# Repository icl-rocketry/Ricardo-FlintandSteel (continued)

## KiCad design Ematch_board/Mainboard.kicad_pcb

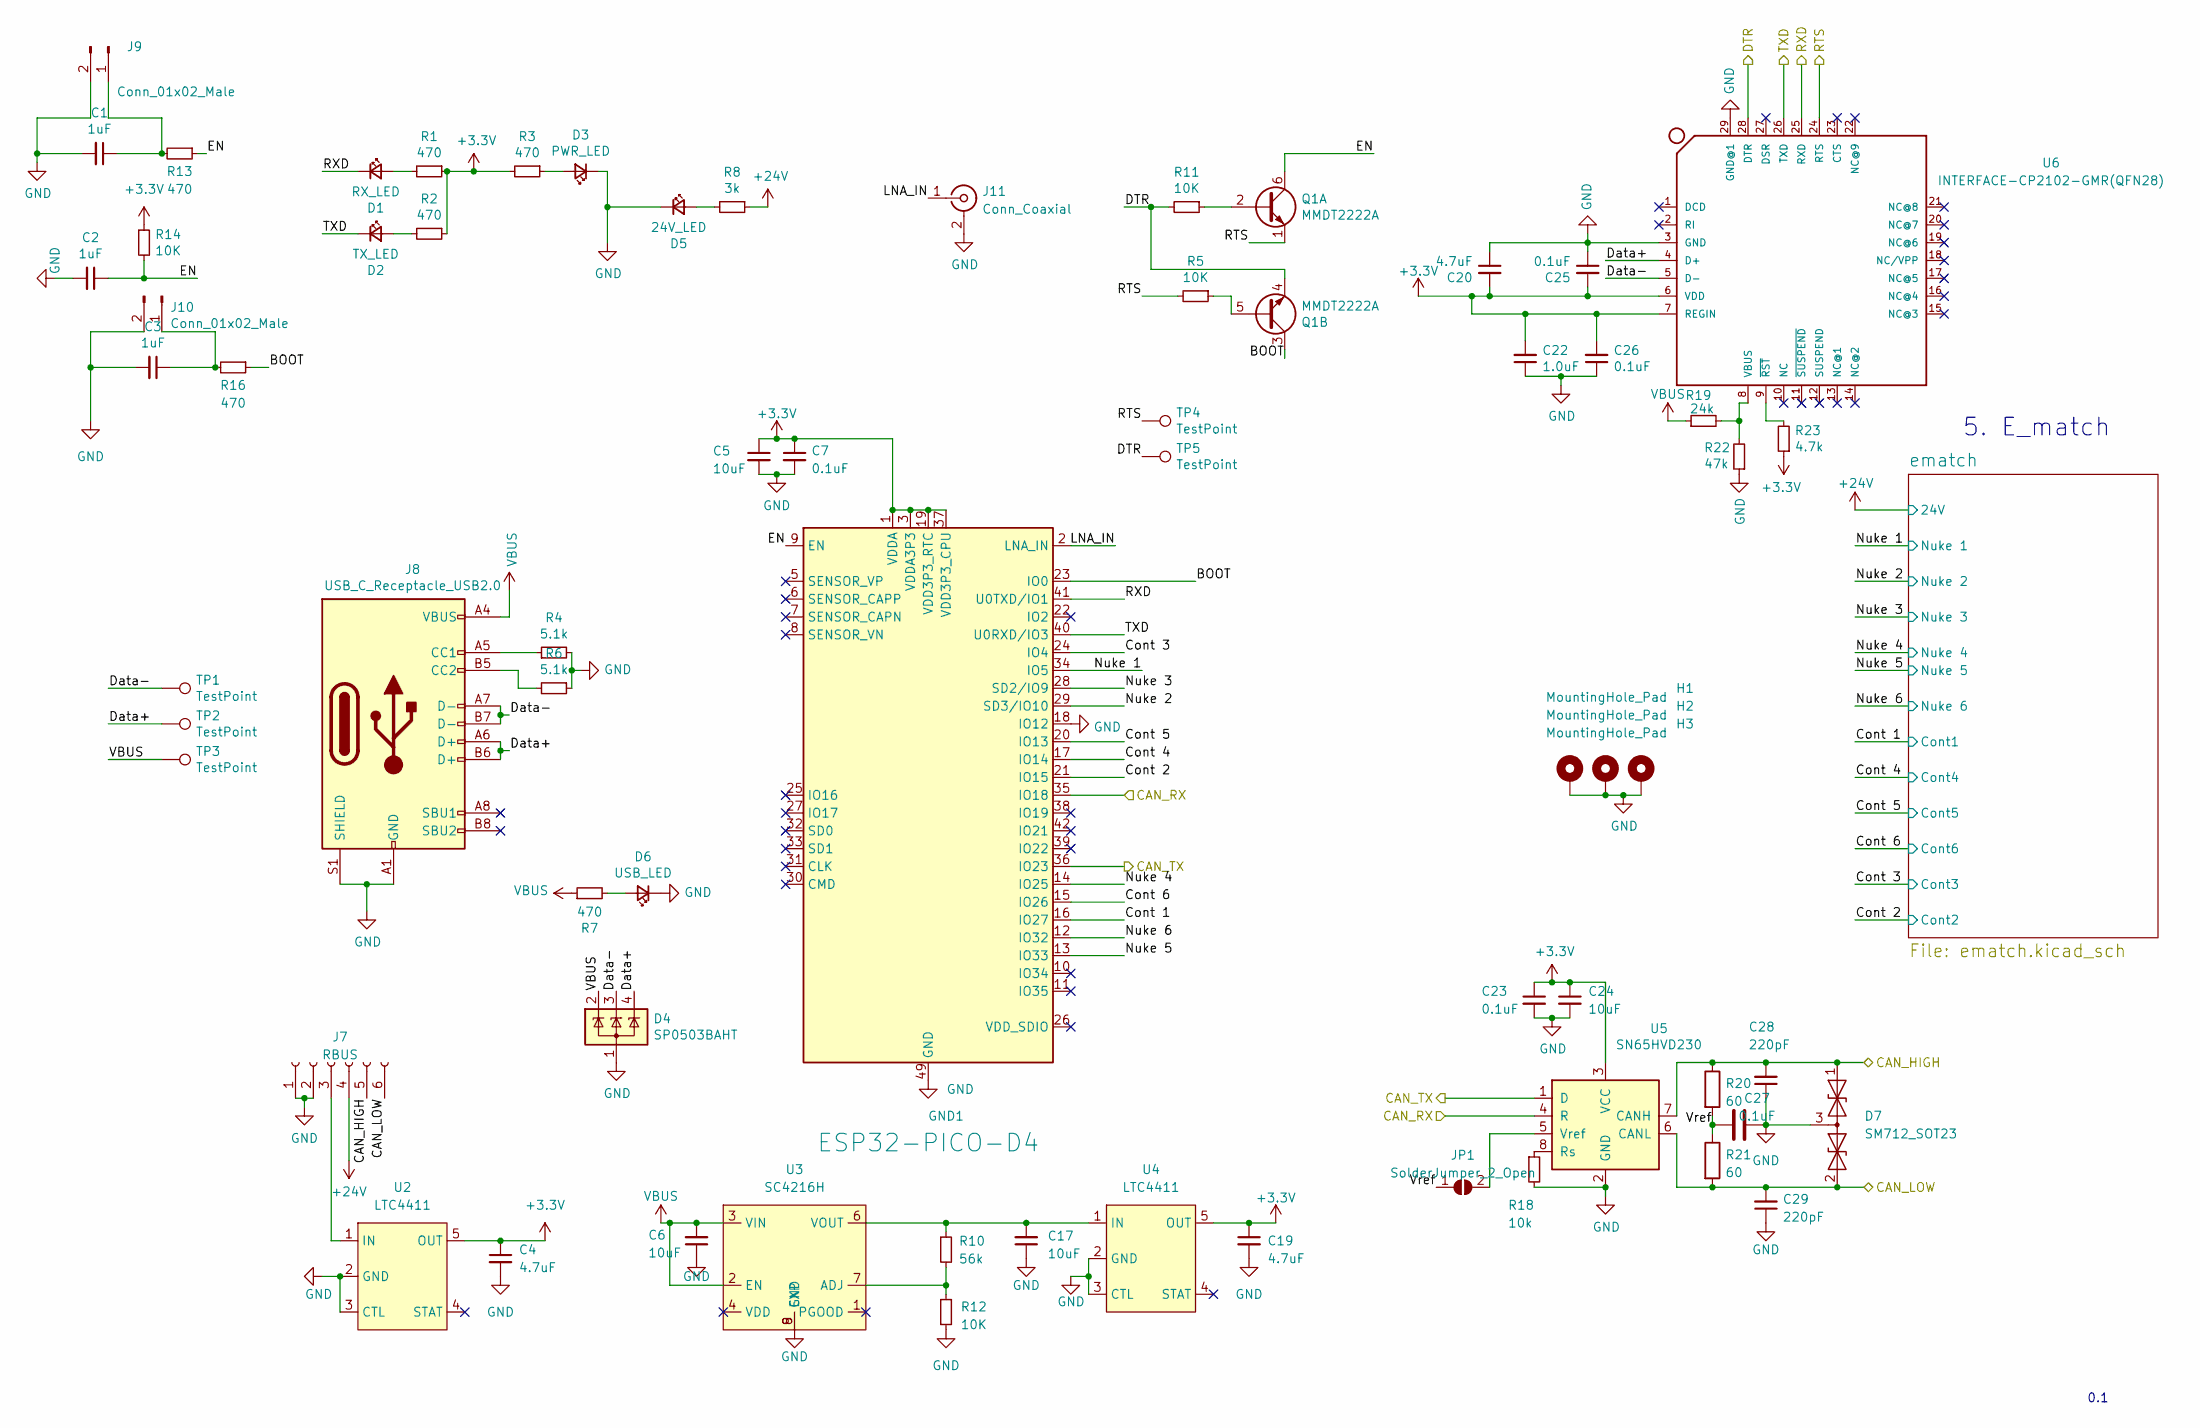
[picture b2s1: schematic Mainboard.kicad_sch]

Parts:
C1, C2, C3: 1uF; C_0603_1608Metric
C4, C19, C20: 4.7uF; C_0603_1608Metric
C5, C6, C17, C24: 10uF; C_0603_1608Metric
C7, C23, C25, C26, C27: 0.1uF; C_0603_1608Metric
C22: 1.0uF; C_0603_1608Metric
C28, C29: 220pF; C_0603_1608Metric
D1: RX_LED; LED_0603_1608Metric
D2: TX_LED; LED_0603_1608Metric
D3: PWR_LED; LED_0603_1608Metric
D4: SP0503BAHT; SOT-143
D5: 24V_LED; LED_0603_1608Metric
D6: USB_LED; LED_0603_1608Metric
D7: SM712_SOT23; SOT-23
GND1: ESP32-PICO-D4; QFN-48-1EP_7x7mm_P0.5mm_EP5.3x5.3mm
H1, H2, H3: MountingHole_Pad; MountingHole_3.2mm_M3_DIN965_Pad
J7: RBUS; Molex_Mini-Fit_Jr_5566-06A_2x03_P4.20mm_Vertical
J8: USB_C_Receptacle_USB2.0; USB_C_Receptacle_GCT_USB4085
J9, J10: Conn_01x02_Male; PinHeader_1x02_P2.54mm_Vertical
J11: Conn_Coaxial; U.FL_Molex_MCRF_73412-0110_Vertical
JP1: SolderJumper_2_Open; SolderJumper-2_P1.3mm_Open_RoundedPad1.0x1.5mm
Q1: MMDT2222A; SOT-363_SC-70-6
R1, R2, R3, R7, R13, R16: 470; R_0603_1608Metric
R4, R6: 5.1k; R_0603_1608Metric
R5, R11, R12, R14: 10K; R_0603_1608Metric
R8: 3k; R_0603_1608Metric
R10: 56k; R_0603_1608Metric
R18: 10k; R_0603_1608Metric
R19: 24k; R_0603_1608Metric
R20, R21: 60; R_0603_1608Metric
R22: 47k; R_0603_1608Metric
R23: 4.7k; R_0603_1608Metric
TP1, TP2, TP3, TP4, TP5: TestPoint; TestPoint_Pad_D1.0mm
U2, U4: LTC4411; SOT-23-5
U3: SC4216H; SOIC127P599X175-9N
U5: SN65HVD230; SOIC-8_3.9x4.9mm_P1.27mm
U6: INTERFACE-CP2102-GMR(QFN28); QFN28G_0.5-5X5MM; MPN CP2102-GMR

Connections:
+24V: J7.4, R8.1; also elsewhere on the board
/BOOT: GND1.23 (IO0), Q1.3 (C2), R16.1
/CAN_HIGH: C28.2, D7.1 (A1), J7.5, R20.1, U5.7 (CANH)
/CAN_LOW: C29.2, D7.2 (A2), J7.6, R21.2, U5.6 (CANL)
/CAN_RX: GND1.35 (IO18), U5.4 (R)
/CAN_TX: GND1.36 (IO23), U5.1 (D)
/Cont 1: GND1.16 (IO27); also elsewhere on the board
/Cont 2: GND1.21 (IO15); also elsewhere on the board
/Cont 3: GND1.24 (IO4); also elsewhere on the board
/Cont 4: GND1.17 (IO14); also elsewhere on the board
/Cont 5: GND1.20 (IO13); also elsewhere on the board
/Cont 6: GND1.15 (IO26); also elsewhere on the board
/DTR: Q1.4 (E2), R11.2, TP5.1, U6.28 (DTR)
/Data+: D4.4 (K), J8.A6 (D+), J8.B6 (D+), TP2.1, U6.4 (D+)
/Data-: D4.3 (K), J8.A7 (D-), J8.B7 (D-), TP1.1, U6.5 (D-)
/EN: C2.1, GND1.9 (EN), Q1.6 (C1), R13.1, R14.2
/LNA_IN: GND1.2 (LNA_IN), J11.1 (In)
/Nuke 1: GND1.34 (IO5); also elsewhere on the board
/Nuke 2: GND1.29 (SD3/IO10); also elsewhere on the board
/Nuke 3: GND1.28 (SD2/IO9); also elsewhere on the board
/Nuke 4: GND1.14 (IO25); also elsewhere on the board
/Nuke 5: GND1.13 (IO33); also elsewhere on the board
/Nuke 6: GND1.12 (IO32); also elsewhere on the board
/RTS: Q1.1 (E1), R5.2, TP4.1, U6.24 (RTS)
/RXD: D1.1 (K), GND1.41 (U0TXD/IO1), U6.25 (RXD)
/TXD: D2.1 (K), GND1.40 (U0RXD/IO3), U6.26 (TXD)
/Vref: C27.1, JP1.1 (A), R20.2, R21.1
GND: C1.2, C2.2, C3.2, C4.2, C5.2, C6.1, C7.2, C17.1, C19.2, C20.1, C22.1, C23.2, C24.2, C25.1, C26.1, C27.2, C28.1, C29.1, D3.1 (K), D4.1 (A), D5.1 (K), D6.1 (K), D7.3 (common), GND1.18 (IO12), GND1.49 (GND), H1.1, H2.1, H3.1, J7.1, J7.2, J8.A1 (GND), J8.A12 (GND), J8.B1 (GND), J8.B12 (GND), J8.S1 (SHIELD), J9.2, J10.2, J11.2 (Ext), R4.2, R6.1, R12.2, R18.2, R22.1, U2.2 (GND), U2.3 (CTL), U3.8 (GND), U3.9 (EXP), U4.2 (GND), U4.3 (CTL), U5.2 (GND), U6.3 (GND), U6.29 (GND@1); also elsewhere on the board
unnamed: C1.1, J9.1, R13.2
unnamed: C3.1, J10.1, R16.2
unnamed: C17.2, R10.1, U3.6 (VOUT), U4.1 (IN)
unnamed: D1.2 (A), R1.2
unnamed: D2.2 (A), R2.2
unnamed: D3.2 (A), R3.1
unnamed: D5.2 (A), R8.2
unnamed: D6.2 (A), R7.2
unnamed: J7.3, U2.1 (IN)
unnamed: J8.A5 (CC1), R4.1
unnamed: J8.B5 (CC2), R6.2
unnamed: JP1.2 (B), U5.5 (Vref)
unnamed: Q1.2 (B1), R11.1
unnamed: Q1.5 (B2), R5.1
unnamed: R10.2, R12.1, U3.7 (ADJ)
unnamed: R18.1, U5.8 (Rs)
unnamed: R19.2, R22.2, U6.8 (VBUS)
unnamed: R23.2, U6.9 (~RST)
VBUS: C6.2, D4.2 (K), J8.A4 (VBUS), J8.A9 (VBUS), J8.B4 (VBUS), J8.B9 (VBUS), R7.1, R19.1, TP3.1, U3.2 (EN), U3.3 (VIN)

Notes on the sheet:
5. E_match
0.1

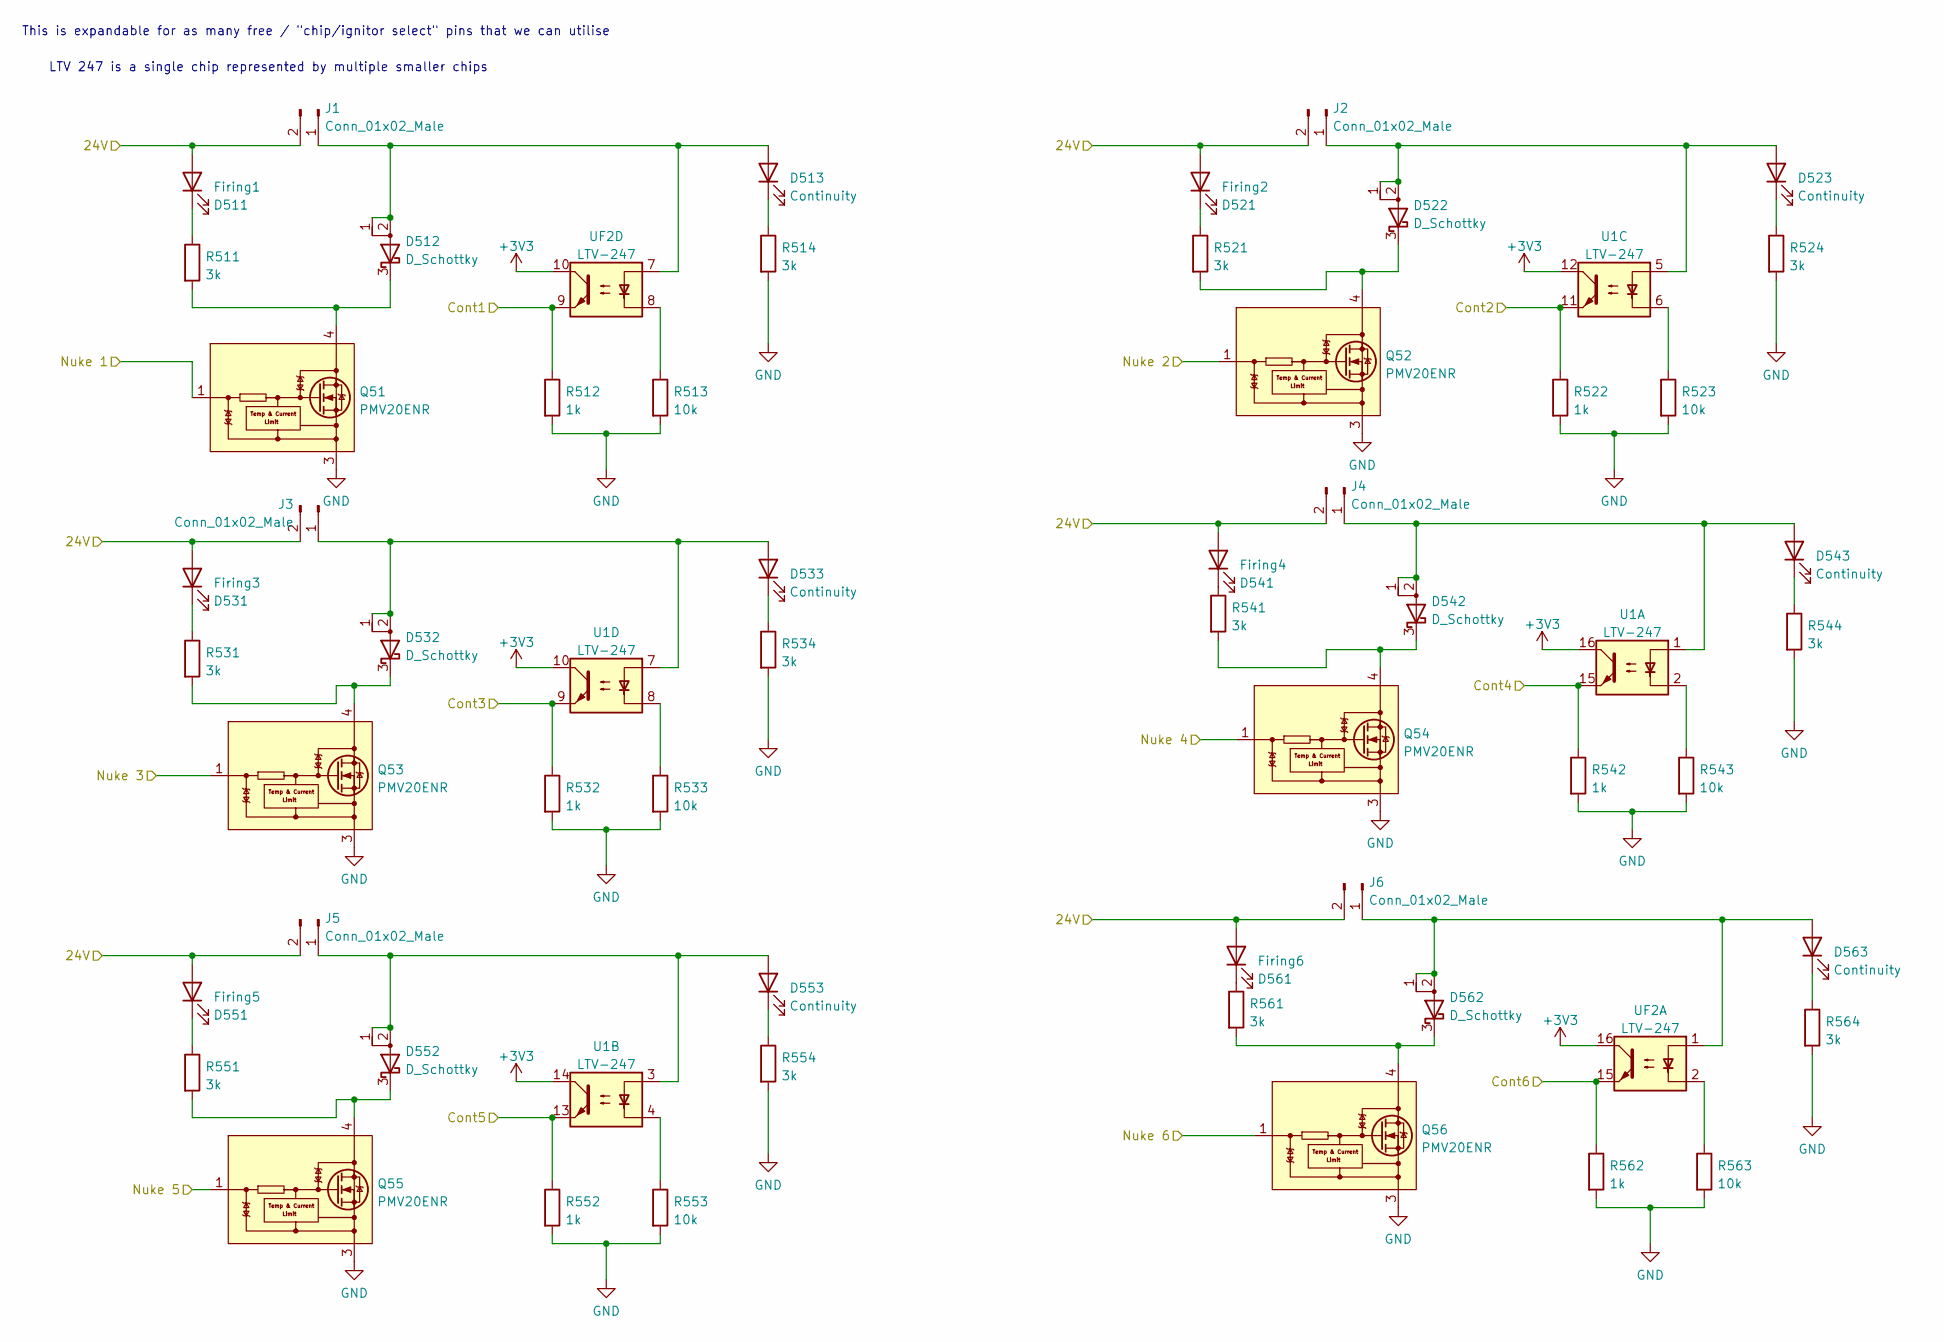
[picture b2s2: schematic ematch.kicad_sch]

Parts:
D512, D522, D532, D542, D552, D562: D_Schottky; TO-277B
D513, D523, D533, D543, D553, D563: Continuity; LED_0603_1608Metric
Firing1: D511; LED_0603_1608Metric
Firing2: D521; LED_0603_1608Metric
Firing3: D531; LED_0603_1608Metric
Firing4: D541; LED_0603_1608Metric
Firing5: D551; LED_0603_1608Metric
Firing6: D561; LED_0603_1608Metric
J1, J2, J3, J4, J5, J6: Conn_01x02_Male; TerminalBlock_TE_282834-2_1x02_P2.54mm_Horizontal
Q51, Q52, Q53, Q54, Q55, Q56: PMV20ENR; SOT-223
R511, R514, R521, R524, R531, R534, R541, R544, R551, R554, R561, R564: 3k; R_0603_1608Metric
R512, R522, R532, R542, R552, R562: 1k; R_0603_1608Metric
R513, R523, R533, R543, R553, R563: 10k; R_0603_1608Metric
U1: LTV-247; SOP-16_4.4x10.4mm_P1.27mm
UF2: LTV-247; SOP-16_4.4x10.4mm_P1.27mm

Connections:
+24V: Firing1.2 (A), Firing2.2 (A), Firing3.2 (A), Firing4.2 (A), Firing5.2 (A), Firing6.2 (A), J1.2, J2.2, J3.2, J4.2, J5.2, J6.2; also elsewhere on the board
/Cont 1: R512.1, UF2.9; also elsewhere on the board
/Cont 2: R522.1, U1.11; also elsewhere on the board
/Cont 3: R532.1, U1.9; also elsewhere on the board
/Cont 4: R542.1, U1.15; also elsewhere on the board
/Cont 5: R552.1, U1.13; also elsewhere on the board
/Cont 6: R562.1, UF2.15; also elsewhere on the board
/Nuke 1: Q51.1 (G); also elsewhere on the board
/Nuke 2: Q52.1 (G); also elsewhere on the board
/Nuke 3: Q53.1 (G); also elsewhere on the board
/Nuke 4: Q54.1 (G); also elsewhere on the board
/Nuke 5: Q55.1 (G); also elsewhere on the board
/Nuke 6: Q56.1 (G); also elsewhere on the board
GND: Q51.3 (S), Q52.3 (S), Q53.3 (S), Q54.3 (S), Q55.3 (S), Q56.3 (S), R512.2, R513.2, R514.2, R522.2, R523.2, R524.2, R532.2, R533.2, R534.2, R542.2, R543.2, R544.2, R552.2, R553.2, R554.2, R562.2, R563.2, R564.2; also elsewhere on the board
unnamed: D512.1 (A), D512.2 (A), D513.2 (A), J1.1, UF2.7
unnamed: D512.3 (K), Q51.2 (D), Q51.4 (D), R511.2
unnamed: D513.1 (K), R514.1
unnamed: D522.1 (A), D522.2 (A), D523.2 (A), J2.1, U1.5
unnamed: D522.3 (K), Q52.2 (D), Q52.4 (D), R521.2
unnamed: D523.1 (K), R524.1
unnamed: D532.1 (A), D532.2 (A), D533.2 (A), J3.1, U1.7
unnamed: D532.3 (K), Q53.2 (D), Q53.4 (D), R531.2
unnamed: D533.1 (K), R534.1
unnamed: D542.1 (A), D542.2 (A), D543.2 (A), J4.1, U1.1
unnamed: D542.3 (K), Q54.2 (D), Q54.4 (D), R541.2
unnamed: D543.1 (K), R544.1
unnamed: D552.1 (A), D552.2 (A), D553.2 (A), J5.1, U1.3
unnamed: D552.3 (K), Q55.2 (D), Q55.4 (D), R551.2
unnamed: D553.1 (K), R554.1
unnamed: D562.1 (A), D562.2 (A), D563.2 (A), J6.1, UF2.1
unnamed: D562.3 (K), Q56.2 (D), Q56.4 (D), R561.2
unnamed: D563.1 (K), R564.1
unnamed: Firing1.1 (K), R511.1
unnamed: Firing2.1 (K), R521.1
unnamed: Firing3.1 (K), R531.1
unnamed: Firing4.1 (K), R541.1
unnamed: Firing5.1 (K), R551.1
unnamed: Firing6.1 (K), R561.1
unnamed: R513.1, UF2.8
unnamed: R523.1, U1.6
unnamed: R533.1, U1.8
unnamed: R543.1, U1.2
unnamed: R553.1, U1.4
unnamed: R563.1, UF2.2

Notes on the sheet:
This is expandable for as many free / "chip/ignitor select" pins that we can utilise
LTV 247 is a single chip represented by multiple smaller chips

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
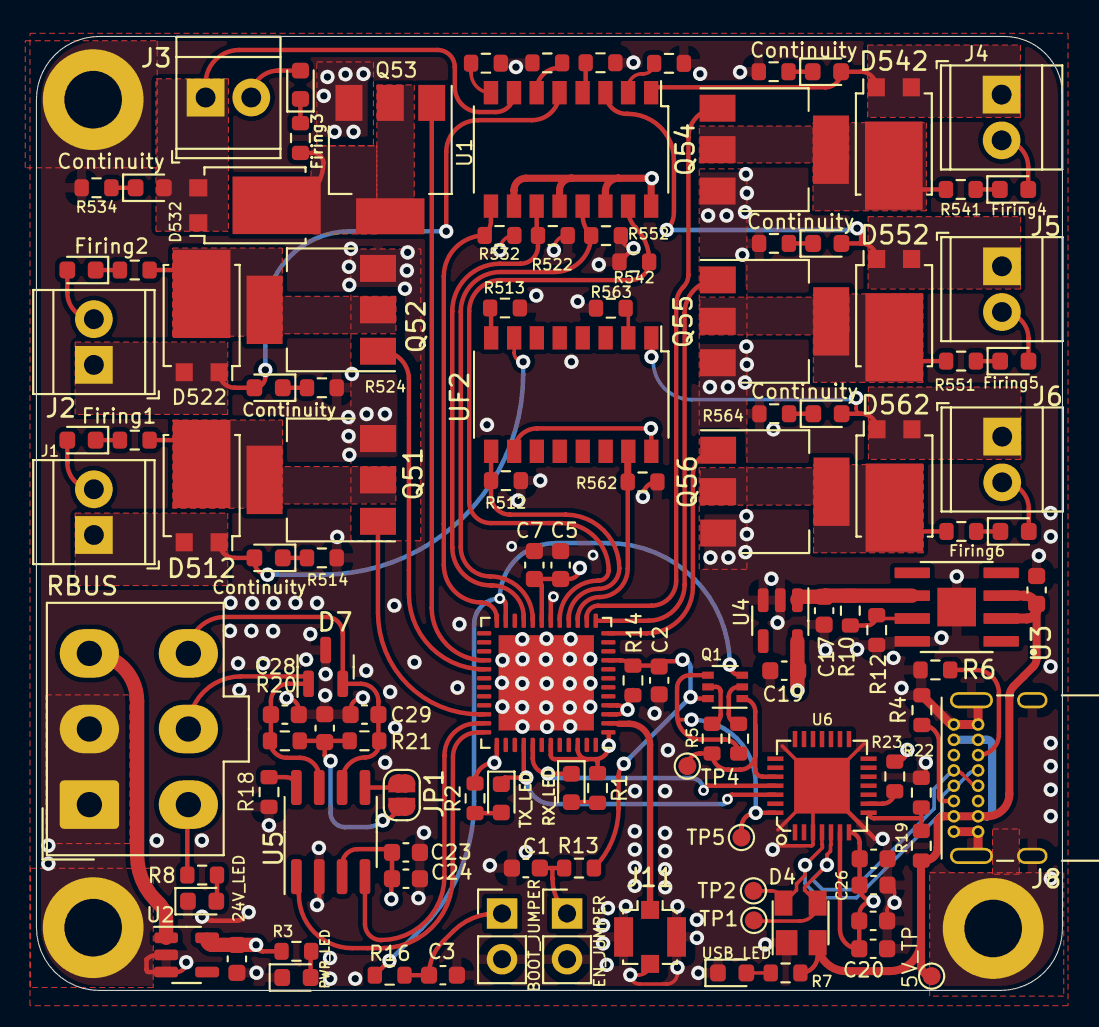
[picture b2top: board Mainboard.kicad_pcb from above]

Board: 4 copper layers, 57.0 x 53.0 mm, 122 parts (0 on the bottom side), 78 nets.

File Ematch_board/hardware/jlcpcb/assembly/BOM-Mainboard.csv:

Comment,Designator,Footprint,LCSC
120,R522,R_0603_1608Metric,
3k,R8,R_0603_1608Metric,
D511,Firing1,LED_0603_1608Metric,
USB_C_Receptacle_USB2.0,J8,USB_C_Receptacle_GCT_USB4085,
Conn_01x02_Male,J10,PinHeader_1x02_P2.54mm_Vertical,
10uF,C24,C_0603_1608Metric,
TestPoint,TP5,TestPoint_Pad_D1.0mm,
5.1k,R6,R_0603_1608Metric,
Continuity,D523,LED_0603_1608Metric,
Continuity,D543,LED_0603_1608Metric,
0.1uF,C23,C_0603_1608Metric,
0.1uF,C7,C_0603_1608Metric,
TestPoint,TP2,TestPoint_Pad_D1.0mm,
Conn_Coaxial,J11,U.FL_Molex_MCRF_73412-0110_Vertical,
5.1k,R4,R_0603_1608Metric,
220pF,C28,C_0603_1608Metric,
PMV20ENR,Q53,SOT-223,
D541,Firing4,LED_0603_1608Metric,
Conn_01x02_Male,J2,TerminalBlock_TE_282834-2_1x02_P2.54mm_Horizontal,
10k,R523,R_0603_1608Metric,
120,R531,R_0603_1608Metric,
10k,R553,R_0603_1608Metric,
Conn_01x02_Male,J1,TerminalBlock_TE_282834-2_1x02_P2.54mm_Horizontal,
Continuity,D563,LED_0603_1608Metric,
10k,R543,R_0603_1608Metric,
D551,Firing5,LED_0603_1608Metric,
10k,R563,R_0603_1608Metric,
Conn_01x02_Male,J9,PinHeader_1x02_P2.54mm_Vertical,
D531,Firing3,LED_0603_1608Metric,
Continuity,D513,LED_0603_1608Metric,
1uF,C3,C_0603_1608Metric,
PMV20ENR,Q54,SOT-223,
470,R7,R_0603_1608Metric,
LTV-247,U1,SOP-16_4.4x10.4mm_P1.27mm,
Conn_01x02_Male,J3,TerminalBlock_TE_282834-2_1x02_P2.54mm_Horizontal,
4.7uF,C4,C_0603_1608Metric,
10uF,C17,C_0603_1608Metric,
0.1uF,C27,C_0603_1608Metric,
10uF,C6,C_0603_1608Metric,
D_Schottky,D562,TO-277B,
SM712_SOT23,D7,SOT-23,
RX_LED,D1,LED_0603_1608Metric,
LTC4411,U2,SOT-23-5,
TestPoint,TP4,TestPoint_Pad_D1.0mm,
PMV20ENR,Q55,SOT-223,
MountingHole_Pad,H3,MountingHole_3.2mm_M3_DIN965_Pad,
120,R511,R_0603_1608Metric,
10K,R14,R_0603_1608Metric,
MountingHole_Pad,H2,MountingHole_3.2mm_M3_DIN965_Pad,
10K,R11,R_0603_1608Metric,
4.7uF,C20,C_0603_1608Metric,
0.1uF,C25,C_0603_1608Metric,
120,R562,R_0603_1608Metric,
ESP32-PICO-D4,GND1,QFN-48-1EP_7x7mm_P0.5mm_EP5.3x5.3mm,
SN65HVD230,U5,SOIC-8_3.9x4.9mm_P1.27mm,
D_Schottky,D522,TO-277B,
Conn_01x02_Male,J6,TerminalBlock_TE_282834-2_1x02_P2.54mm_Horizontal,
INTERFACE-CP2102-GMR(QFN28),U6,QFN28G_0.5-5X5MM,
10K,R5,R_0603_1608Metric,
Continuity,D553,LED_0603_1608Metric,
120,R521,R_0603_1608Metric,
RBUS,J7,Molex_Mini-Fit_Jr_5566-06A_2x03_P4.20mm_Vertical,
220pF,C29,C_0603_1608Metric,
PMV20ENR,Q51,SOT-223,
1uF,C2,C_0603_1608Metric,
Continuity,D533,LED_0603_1608Metric,
4.7k,R23,R_0603_1608Metric,
10k,R533,R_0603_1608Metric,
120,R561,R_0603_1608Metric,
PMV20ENR,Q52,SOT-223,
24V_LED,D5,LED_0603_1608Metric,
1uF,C1,C_0603_1608Metric,
D_Schottky,D532,TO-277B,
60,R21,R_0603_1608Metric,
D561,Firing6,LED_0603_1608Metric,
MMDT2222A,Q1,SOT-363_SC-70-6,
D521,Firing2,LED_0603_1608Metric,
0.1uF,C26,C_0603_1608Metric,
10k,R513,R_0603_1608Metric,
120,R541,R_0603_1608Metric,
1.0uF,C22,C_0603_1608Metric,
470,R16,R_0603_1608Metric,
56k,R10,R_0603_1608Metric,
USB_LED,D6,LED_0603_1608Metric,
120,R552,R_0603_1608Metric,
SolderJumper_2_Open,JP1,SolderJumper-2_P1.3mm_Open_RoundedPad1.0x1.5mm,
LTV-247,UF2,SOP-16_4.4x10.4mm_P1.27mm,
47k,R22,R_0603_1608Metric,
D_Schottky,D542,TO-277B,
PWR_LED,D3,LED_0603_1608Metric,
120,R532,R_0603_1608Metric,
120,R512,R_0603_1608Metric,
D_Schottky,D512,TO-277B,
10K,R12,R_0603_1608Metric,
120,R551,R_0603_1608Metric,
470,R2,R_0603_1608Metric,
LTC4411,U4,SOT-23-5,
10k,R18,R_0603_1608Metric,
120,R542,R_0603_1608Metric,
4.7uF,C19,C_0603_1608Metric,
470,R1,R_0603_1608Metric,
D_Schottky,D552,TO-277B,
MountingHole_Pad,H1,MountingHole_3.2mm_M3_DIN965_Pad,
470,R13,R_0603_1608Metric,
TX_LED,D2,LED_0603_1608Metric,
60,R20,R_0603_1608Metric,
TestPoint,TP3,TestPoint_Pad_D1.0mm,
24k,R19,R_0603_1608Metric,
TestPoint,TP1,TestPoint_Pad_D1.0mm,
Conn_01x02_Male,J5,TerminalBlock_TE_282834-2_1x02_P2.54mm_Horizontal,
PMV20ENR,Q56,SOT-223,
SC4216H,U3,SOIC127P599X175-9N,
10uF,C5,C_0603_1608Metric,
Conn_01x02_Male,J4,TerminalBlock_TE_282834-2_1x02_P2.54mm_Horizontal,
470,R3,R_0603_1608Metric,
SP0503BAHT,D4,SOT-143,

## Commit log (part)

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2021-12-04 Initial rev of e-match board (adapted from sensorboard schematic)
    Replaced all the ADCs with 4 e-match circuits
2021-12-04 Added arming LED
    Arming LED is to turn ON when circuit is primed - after 5s of charging capacitor / boot
    A more precise way to do this would probably be to hook up another MOSFET to regulate input voltage (so you can control capacitor charging from the ESP)
2021-12-04 Added arming LED 2
    Github Desktop threw me a weird error, so here's a second commit
2021-12-04 Schematic comments + minor fixes
2021-12-15 Updated number of ematches
    Increased e match count from 4->6 as requested (2 spares)
2022-03-12 removed other files
2022-04-17 Unzipped files + implemented schematic review feedback
2022-05-14 changed LDO passives, changed filestructure
2022-05-14 removed ground traces
2022-05-16 routed thicker 24V traces and moved some components
2022-05-17 changed schottky diode FP and rearranged mosfets + screw terminals
2022-05-18 completed layout for screw terminals, moved some LEDs
2022-05-18 initial routing of cont and nuke traces
2022-05-21 completed routing, changed antenna for U.FL connector
2022-05-21 created GND planes and fixed zone priority to prevent shorting nets
2022-05-24 Made front silkscreen intelligible
2022-05-24 Added flint and steel name and picture
2022-05-24 Added writepad and iclr logo to back silkscreen
2022-05-24 Removed thermal relief on RBUS
2022-05-31 Added names on back silkscreen, implemented Kiran's mini review
2022-05-31 fixed front silkscreen after board re-dimension
2022-06-21 Added version numbering
2022-06-28 Changed 24V LED resistor value
2022-06-29 Changed LDO symbol
2022-07-06 Changed boot and EN jumper caps
2022-07-06 set values for can passives
2022-07-06 fixed unroute nets and changed LED resistor values
2022-07-06 moved nuke channels from input only pins, changed resistor values
2022-07-06 forgot to stage this in the last commit
2022-07-08 Changed autoprogrammer caps to 1uF
2022-07-11 Added ICLR logo and fixed antenna line impedance
2022-07-14 Removed CAN resistors
2022-07-21 DRC fixes
2022-07-26 Changed ESP32 pin assignment from special IO pins
2022-07-29 Fixed pin assigments again
2022-08-02 updated leds on ematch board and re-routed
2022-09-09 fixed canbus;
2022-09-30 added net conf
2022-10-04 remove serial print which was causing issues over serial debug
2023-02-24 restructured folders, updated to s3 template, scaled down to 4 channels
2023-02-24 whatever gitkraken missed
2023-03-14 schematic done? + footprints assigned
2023-03-15 started pyro channel layout
2023-03-16 pyro channels & tiny buck passives
2023-03-18 I had to get back out of bed to push this commit
2023-03-27 I don't remember what I did but I have to move these files to my desktop
2023-03-28 High power side nearly done
2023-03-29 high V side finished, CAN circuit and ESP left to place
2023-03-30 finished? (pre-review)
2023-03-30 changed buck FB resistors to actual values
2023-06-11 no buck, technically complete but I still want to make some changes
2023-06-13 removed can caps, better via stitching, fini?
2023-06-13 forgor about the gerbers but whatever
2023-06-13 teardrops
2023-07-06 Kiran's review
2023-08-15 removing software
2023-08-15 adding firmware
2023-08-15 adding firmware finally
2023-08-15 fixed submodules (how does this happen every time??)
2023-08-15 forgor arduino submodule, added can interface, f&s fw done lol?
2023-08-16 CAN pins were wrong, systemflags include was in the wrong order
2023-08-18 changed mosfets and added current sense circuit, layout not done
2023-08-20 mostly finished new power layout, needs some vias and i2c routing
2023-08-20 v2.1
2023-08-21 some zone priorities
2023-09-02 changed project name
2023-09-05 v2.1 ordering
2023-09-28 started INA219 sensor driver,pulled submodule main
2023-09-28 removed INA219, fixed Config folder
2023-10-02 updated to latest
2023-10-04 copied in the improved freeram command
2023-10-31 submodules track properly now
2023-11-10 current sensor finally works
2024-01-21 updated to work with new nrc pyro class
2024-02-29 Create LICENSE
2024-05-22 current files on cosmos fns
2024-07-12 Fixed current sensor. FYI, changing a setting after setting calibration register wipes calibration register.
2024-09-03 added high side switch
2024-09-04 v3 hardware I guess
2024-09-04 forgot teardrops
2024-09-04 TVS diode and sized resistor ladder
2024-09-10 ordered F&S v3
2024-09-14 updated libriccore version
2024-10-10 v3 pins
2025-01-11 moved to latest platformio esp32 release - switched to idf5.3
2025-01-11 Cleanup of unused libraries
2025-01-11 Changed partition map to take advantage of 8M flash
2025-01-11 moved arduino to a release commit
2025-01-11 correct commit of libroccore
2025-01-11 remove .pio files from repo
2025-01-12 Added LICENSE
2025-12-27 Always on high side switch
2025-12-27 v4 submodules
2026-03-01 files
2026-03-07 updated after rileys suggestions
2026-03-07 silkscreen changes
2026-03-07 bomba
2026-06-18 add on/off switch pins
2026-06-18 add pyro "adapters" for local use of pyro objects
2026-06-18 arm / disarm pyros based of switches, enforce continuity
2026-06-18 fix: change logger callback to lambda
2026-06-18 remove redundant PYRO in loggers enum
2026-06-18 fix: use COUT for adapter logger callback
2026-06-18 TODOs : adapter.execute() to fire pyros and change pin assignments of switches to correct pin numbers
2026-06-24 tidied up schematic and bom
2026-06-30 add adapter.execute() after arming
2026-06-30 lcd setup and update logic
